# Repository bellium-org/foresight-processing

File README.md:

# Foresight Processing

## Overview
The processing board is responsible for the main processing of the vibration analysis. On board is the ATmega328pb microcontroller, RFM95W LoRa transceiver and ADXL362 accelerometer. In addition there is a NMOS low side switch to turn of the RFM95W and ADXL362 when they are not needed to save power consumption.

## Table of Contents

- [Hardware Setup](#hardware-setup)
- [Imporant Notice](#important-notice)

### Hardware Setup

### Important Notice
- All required components used in this project can be located in the components folder. 
- To add these components into your workspace please follow the instructions from given from each of the individual components. 
- Ensure the digikey submodule is initialise and follow the README to set this up.

## Authors
- Nathan Nguyen

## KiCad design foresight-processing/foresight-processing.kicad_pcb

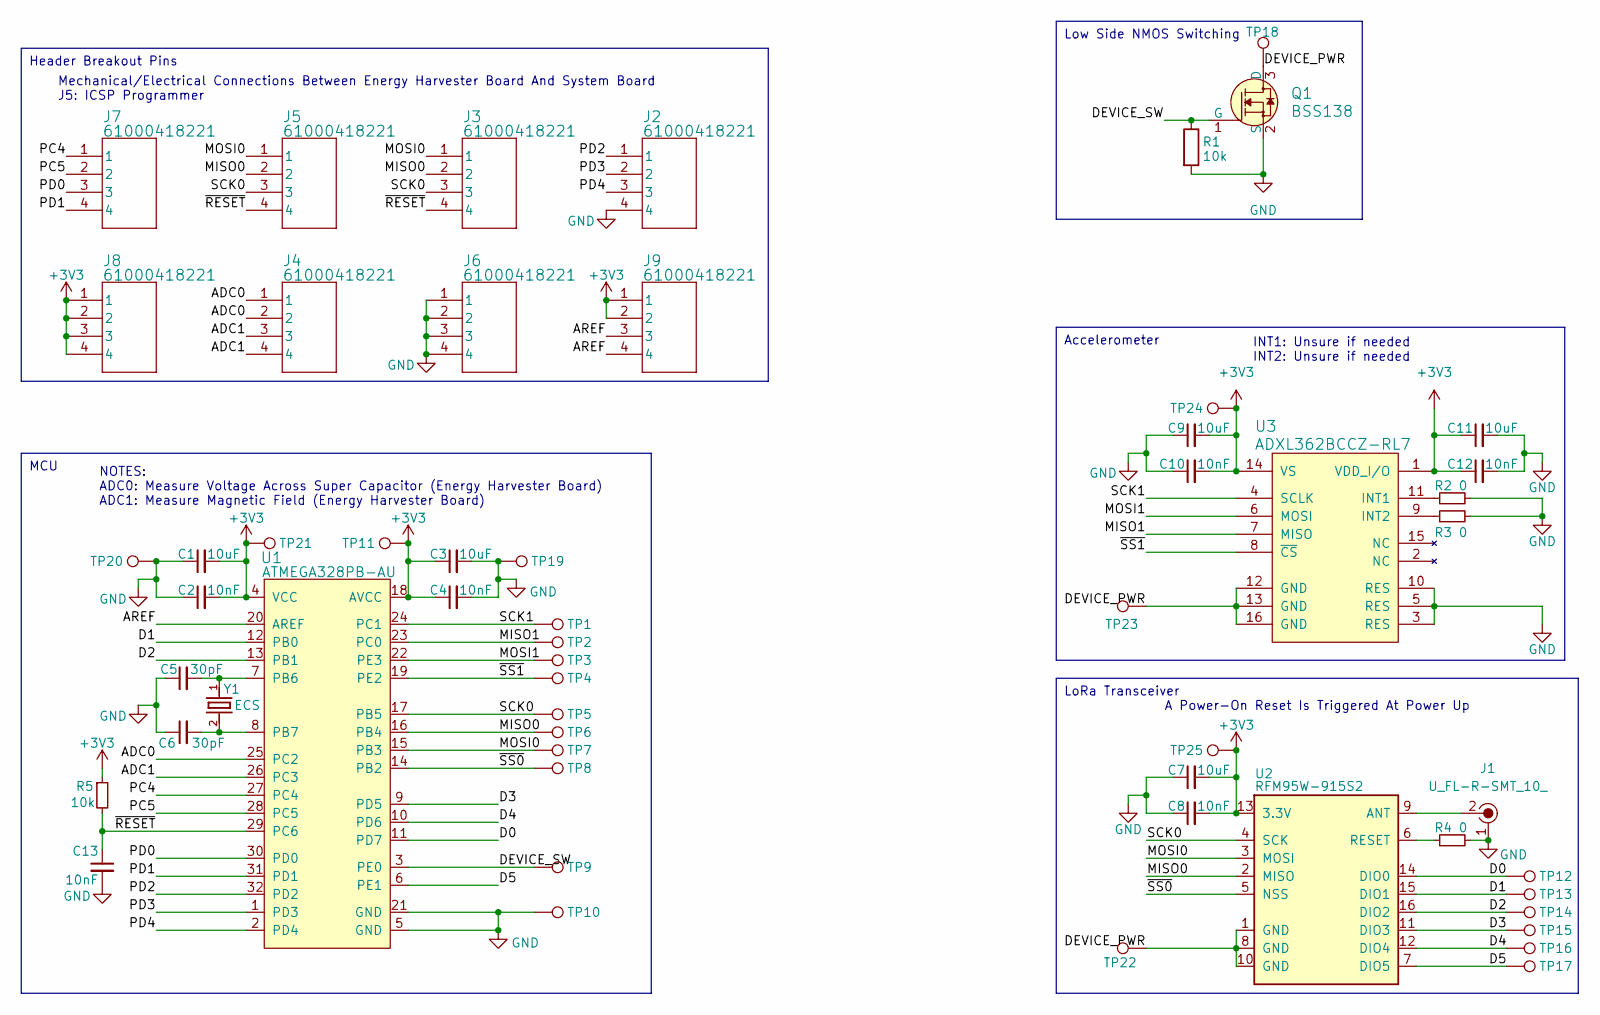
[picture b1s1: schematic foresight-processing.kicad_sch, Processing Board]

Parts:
C1, C3, C7, C9, C11: 10uF; C_0603_1608Metric
C2, C4, C8, C10, C12, C13: 10nF; C_0603_1608Metric
C5, C6: 30pF; C_0603_1608Metric
J1: U_FL-R-SMT_10_; Coax_Conn_U.FL; MPN U.FL-R-SMT(10); Digi-Key_PN H9161CT-ND
J2, J3, J4, J5, J6, J7, J8, J9: 61000418221; 61000418221_WRE
Q1: BSS138; SOT-23_3L_ONS; MPN BSS138; Digi-Key_PN BSS138CT-ND
R1, R5: 10k; R_0603_1608Metric
R2, R3, R4: 0; R_0603_1608Metric
TP1, TP2, TP3, TP4, TP5, TP6, TP7, TP8, TP9, TP10, TP11, TP12, TP13, TP14, TP15, TP16, TP17, TP18, TP19, TP20, TP21, TP22, TP23, TP24, TP25: TestPoint; TestPoint_Pad_D2.0mm
U1: ATMEGA328PB-AU; TQFP-32_7x7mm; MPN ATMEGA328PB-AU; Digi-Key_PN ATMEGA328PB-AU-ND
U2: RFM95W-915S2; HOPERF_RFM9XW_SMD
U3: ADXL362BCCZ-RL7; TFLGA-16_3x3.25mm; MPN ADXL362BCCZ-RL7; Digi-Key_PN ADXL362BCCZ-RL7CT-ND
Y1: ECS; CRYSTAL_ECS-80-18-5PX-TR_ECS

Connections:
+3V3: C1.2, C2.2, C3.1, C4.1, C7.2, C8.2, C9.2, C10.2, C11.1, C12.1, J8.1, J8.2, J8.3, J8.4, J9.1, J9.2, R5.1, TP11.1, TP21.1, TP24.1, TP25.1, U1.4 (VCC), U1.18 (AVCC), U2.13 (3.3V), U3.1 (VDD_I/O), U3.14 (VS)
/ADC0: J4.1, J4.2, U1.25 (PC2)
/ADC1: J4.3, J4.4, U1.26 (PC3)
/AREF: J9.3, J9.4, U1.20 (AREF)
/D0: TP12.1, U1.11 (PD7), U2.14 (DIO0)
/D1: TP13.1, U1.12 (PB0), U2.15 (DIO1)
/D2: TP14.1, U1.13 (PB1), U2.16 (DIO2)
/D3: TP15.1, U1.9 (PD5), U2.11 (DIO3)
/D4: TP16.1, U1.10 (PD6), U2.12 (DIO4)
/D5: TP17.1, U1.6 (PE1), U2.7 (DIO5)
/DEVICE_PWR: Q1.3 (D), TP18.1, TP22.1, TP23.1, U2.1 (GND), U2.8 (GND), U2.10 (GND), U3.12 (GND), U3.13 (GND), U3.16 (GND)
/DEVICE_SW: Q1.1 (G), R1.1, TP9.1, U1.3 (PE0)
/MISO0: J3.2, J5.2, TP6.1, U1.16 (PB4), U2.2 (MISO)
/MISO1: TP2.1, U1.23 (PC0), U3.7 (MISO)
/MOSI0: J3.1, J5.1, TP7.1, U1.15 (PB3), U2.3 (MOSI)
/MOSI1: TP3.1, U1.22 (PE3), U3.6 (MOSI)
/PC4: J7.1, U1.27 (PC4)
/PC5: J7.2, U1.28 (PC5)
/PD0: J7.3, U1.30 (PD0)
/PD1: J7.4, U1.31 (PD1)
/PD2: J2.1, U1.32 (PD2)
/PD3: J2.2, U1.1 (PD3)
/PD4: J2.3, U1.2 (PD4)
/SCK0: J3.3, J5.3, TP5.1, U1.17 (PB5), U2.4 (SCK)
/SCK1: TP1.1, U1.24 (PC1), U3.4 (SCLK)
/~RESET: C13.1, J3.4, J5.4, R5.2, U1.29 (PC6)
/~SS0: TP8.1, U1.14 (PB2), U2.5 (NSS)
/~SS1: TP4.1, U1.19 (PE2), U3.8 (~CS)
GND: C1.1, C2.1, C3.2, C4.2, C5.1, C6.1, C7.1, C8.1, C9.1, C10.1, C11.2, C12.2, C13.2, J1.1, J2.4, J6.1, J6.2, J6.3, J6.4, Q1.2 (S), R1.2, R2.2, R3.2, R4.2, TP10.1, TP19.1, TP20.1, U1.5 (GND), U1.21 (GND), U3.3 (RES), U3.5 (RES), U3.10 (RES)
unnamed: C5.2, U1.7 (PB6), Y1.1
unnamed: C6.2, U1.8 (PB7), Y1.2
unnamed: J1.2, U2.9 (ANT)
unnamed: R4.1, U2.6 (RESET)
unnamed: R2.1, U3.11 (INT1)
unnamed: R3.1, U3.9 (INT2)

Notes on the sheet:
MCU
Accelerometer
Low Side NMOS Switching
LoRa Transceiver
Header Breakout Pins
INT1: Unsure if needed INT2: Unsure if needed
Mechanical/Electrical Connections Between Energy Harvester Board And System Board J5: ICSP Programmer
NOTES: ADC0: Measure Voltage Across Super Capacitor (Energy Harvester Board) ADC1: Measure Magnetic Field (Energy Harvester Board)
A Power-On Reset Is Triggered At Power Up

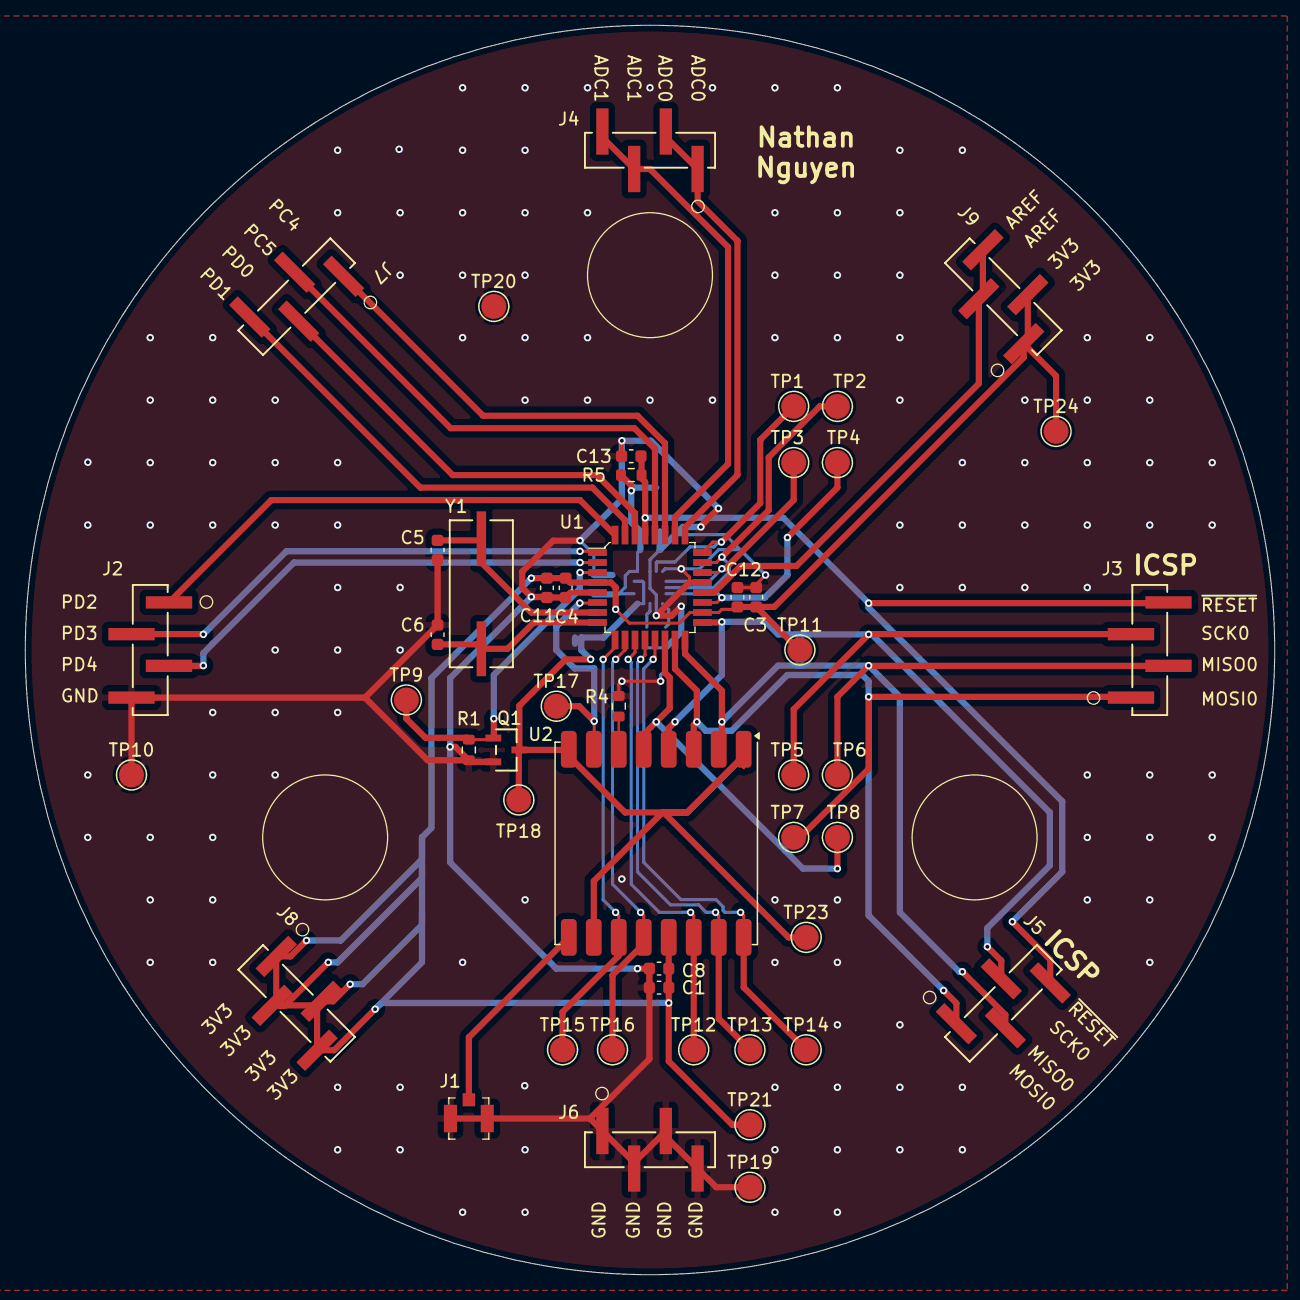
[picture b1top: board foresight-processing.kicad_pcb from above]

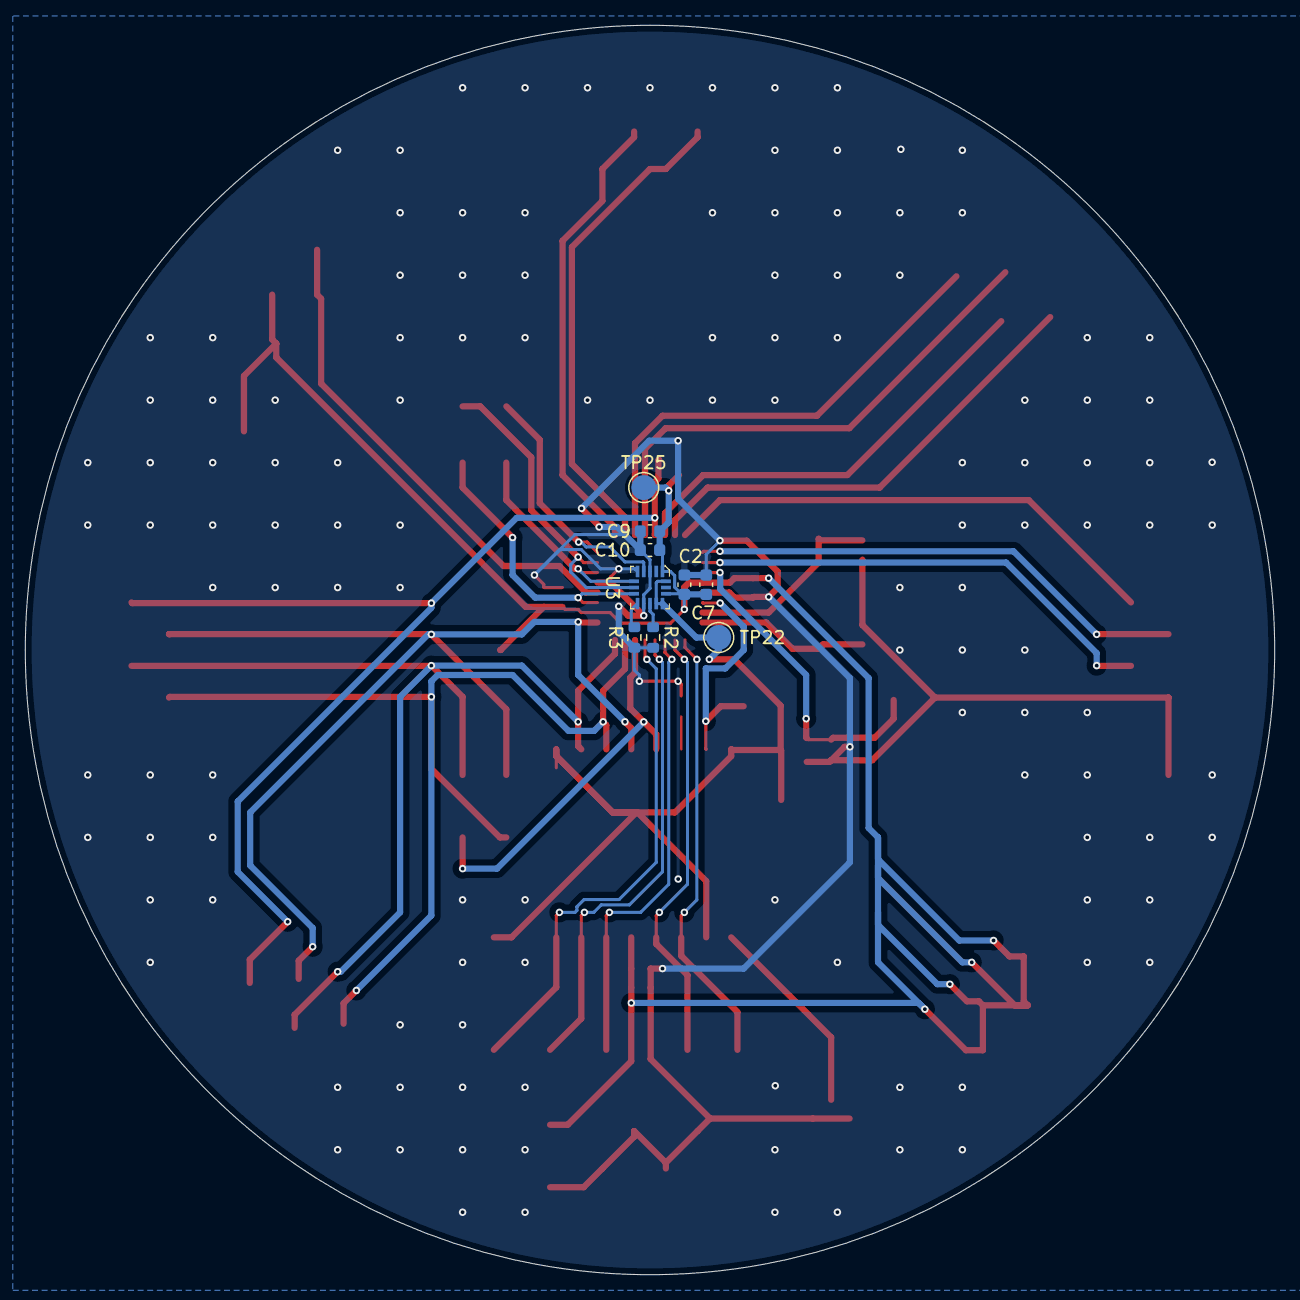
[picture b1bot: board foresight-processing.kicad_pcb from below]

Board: 2 copper layers, 100.0 x 100.0 mm, 57 parts (9 on the bottom side), 35 nets.

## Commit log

2025-03-04 feat: Initial Commit
2025-03-04 Create LICENSE
